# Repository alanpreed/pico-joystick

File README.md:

# pico-joystick
A USB adapter for analogue Gameport joysticks

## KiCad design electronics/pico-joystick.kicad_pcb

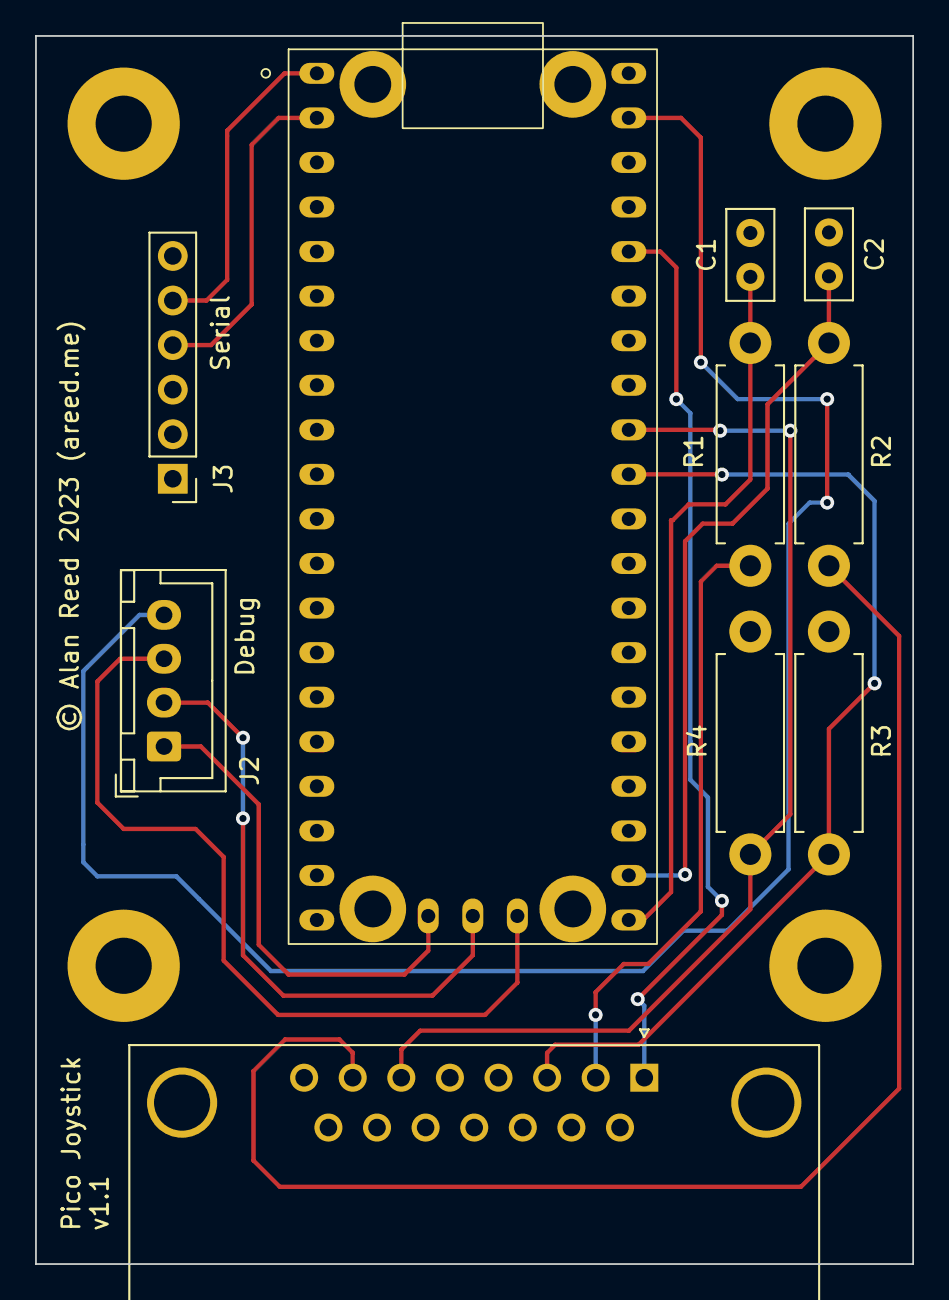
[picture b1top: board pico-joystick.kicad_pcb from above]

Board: 2 copper layers, 50.0 x 70.0 mm, 10 parts (0 on the bottom side), 14 nets.

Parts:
C1, C2: 1n; C_Disc_D5.0mm_W2.5mm_P2.50mm
J1: Gameport socket; DSUB-15_Female_Horizontal_P2.77x2.84mm_EdgePinOffset9.90mm_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
J2: Debug; JST_XH_B4B-XH-A_1x04_P2.50mm_Vertical
J3: Serial; PinHeader_1x06_P2.54mm_Vertical
R1, R2: 1k; R_Axial_DIN0411_L9.9mm_D3.6mm_P12.70mm_Horizontal
R3, R4: 10k; R_Axial_DIN0411_L9.9mm_D3.6mm_P12.70mm_Horizontal
U1: Raspberry Pi Pico; Pi_Pico

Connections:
+3V3: J1.1, U1.36 (3V3(OUT))
GND: C1.2, C2.2, J1.0 (PAD), J1.4, J3.1, R3.2, R4.2, U1.3 (GND), U1.8 (GND), U1.13 (GND), U1.18 (GND), U1.23 (GND), U1.28 (GND), U1.33 (GND), U1.38 (GND)
unnamed: J1.2, R1.1
unnamed: J1.7, R2.1
unnamed: J2.1, U1.41 (SWCLK)
unnamed: J2.2, U1.42 (GND)
unnamed: J2.3, U1.43 (SWDIO)
unnamed: J2.4, U1.39 (VSYS)
unnamed: J3.4, U1.2 (GP1)
unnamed: J3.5, U1.1 (GP0)
unnamed: C1.1, R1.2, U1.21 (GP16)
unnamed: C2.1, R2.2, U1.22 (GP17)
unnamed: J1.3, R3.1, U1.31 (GP26)
unnamed: J1.6, R4.1, U1.32 (GP27)

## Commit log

2023-04-09 Added license
2023-04-09 Initial software implementation
2023-04-10 Added initial PCB design
2023-04-15 Created initial model of the Pico Joystick PCB
2023-04-15 Created initial casework design
2023-05-02 Corrected PCB design
2023-05-13 Fixed overlapping text
2023-05-13 Corrected casework, generated print models
2023-05-18 Added averaging of joystick axes values

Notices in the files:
electronics/pico-joystick.kicad_pcb:
© Alan Reed 2023 (areed.me)
